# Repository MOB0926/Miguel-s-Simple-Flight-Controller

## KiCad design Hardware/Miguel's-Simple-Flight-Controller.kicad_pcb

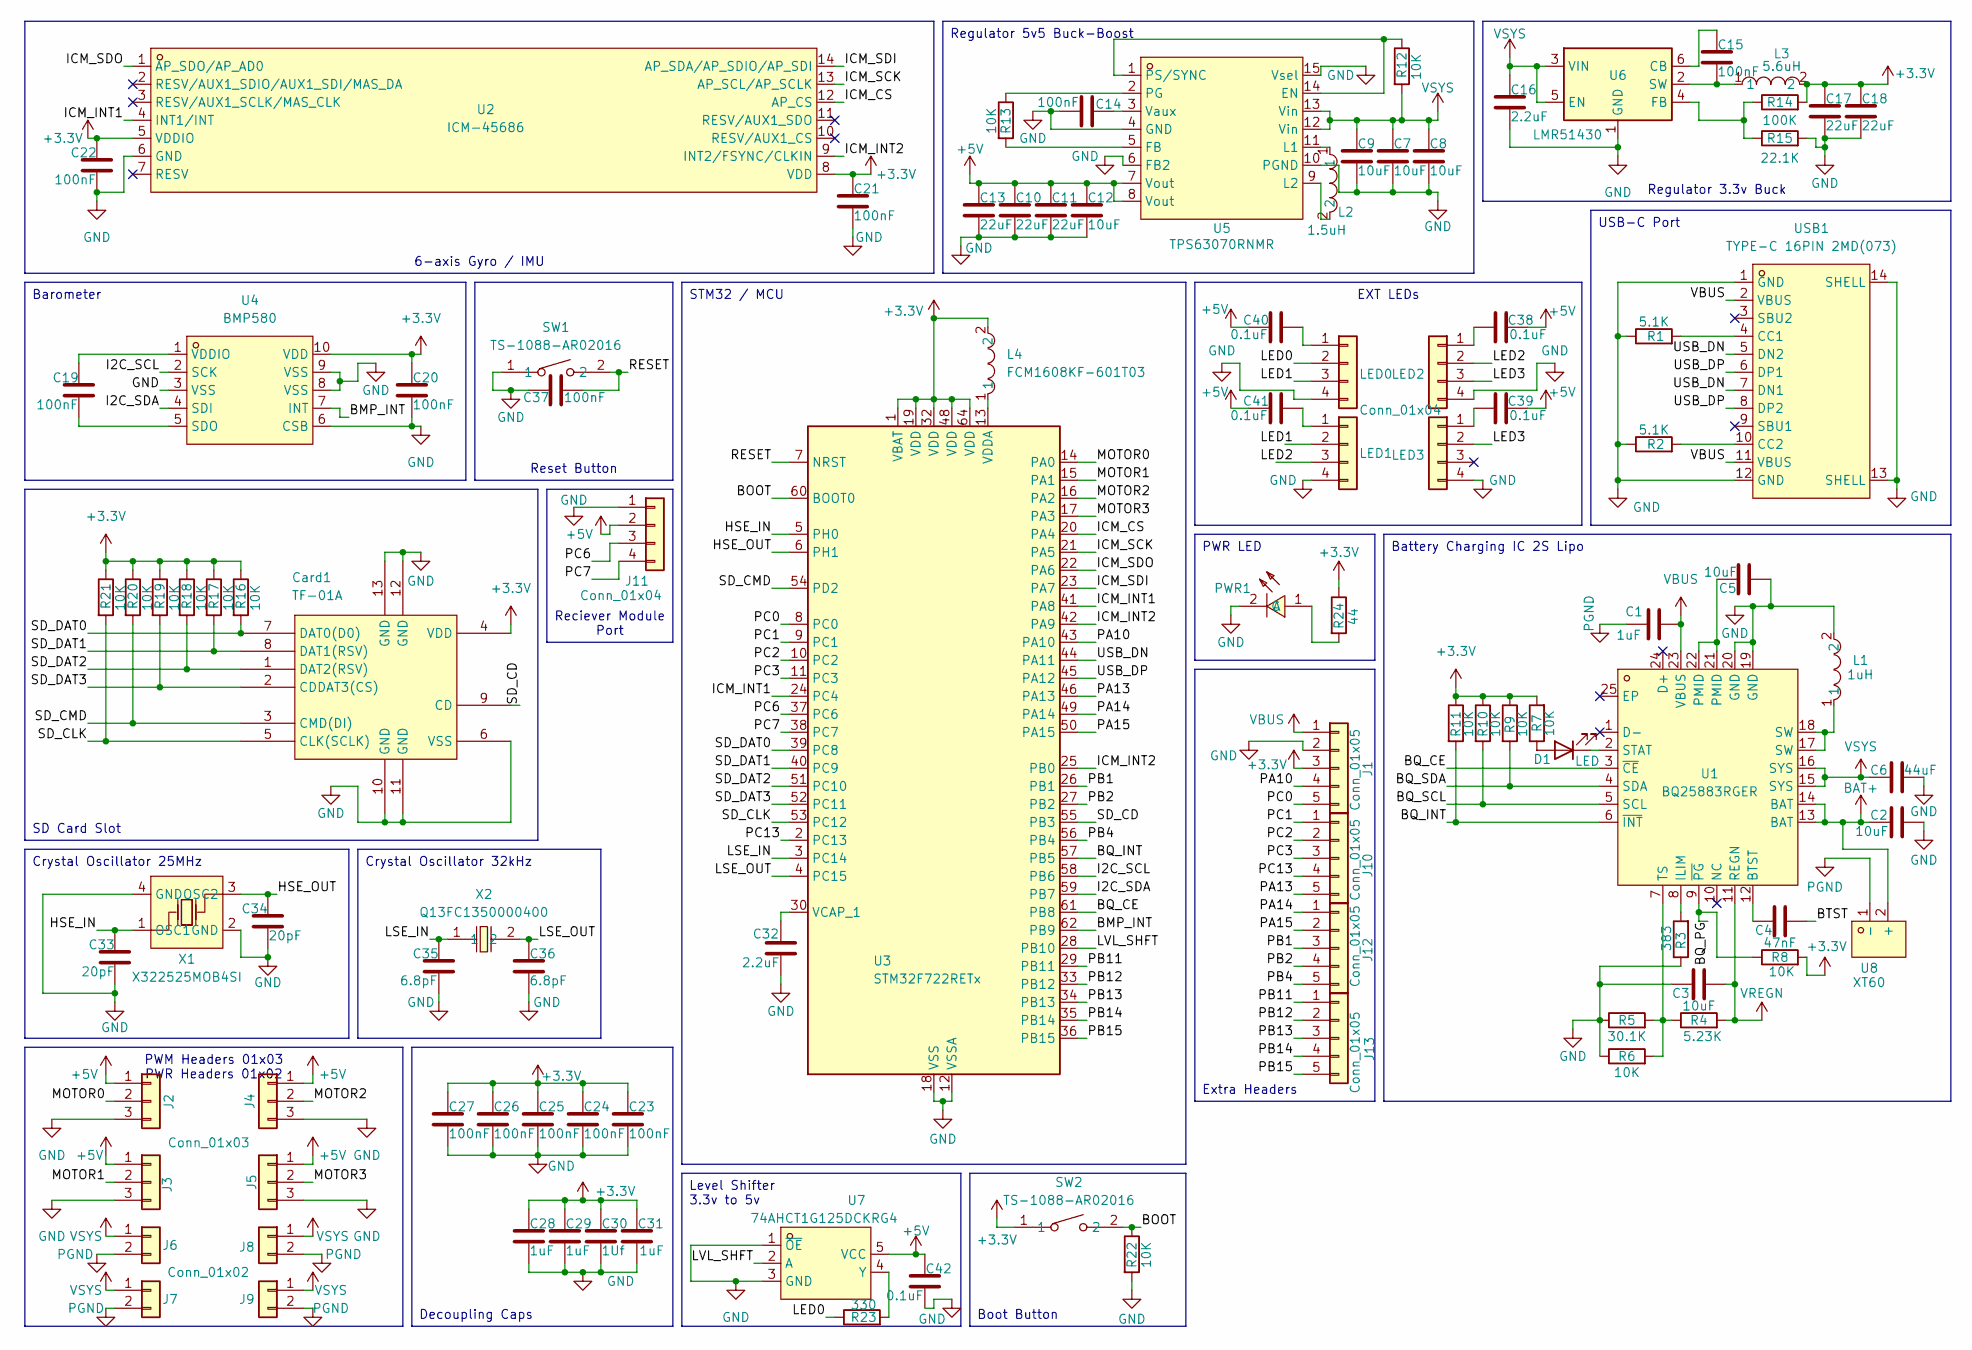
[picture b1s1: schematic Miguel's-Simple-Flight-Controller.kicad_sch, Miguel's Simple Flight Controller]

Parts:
C1, C28, C29, C31: 1uF; C_0402_1005Metric
C2, C3, C5, C7, C8, C9, C12: 10uF; C_0402_1005Metric
C4: 47nF; C_0402_1005Metric
C6: 44uF; C_0805_2012Metric
C10, C11, C13, C17, C18: 22uF; C_0805_2012Metric
C14, C15, C19, C20, C21, C22, C23, C24, C25, C26, C27, C37: 100nF; C_0402_1005Metric
C16, C32: 2.2uF; C_0402_1005Metric
C30: 1Uf; C_0402_1005Metric
C33, C34: 20pF; C_0402_1005Metric
C35, C36: 6.8pF; C_0402_1005Metric
C38, C39, C40, C41, C42: 0.1uF; C_0402_1005Metric
Card1: TF-01A; TF-SMD_TF-01A; LCSC Part C91145
D1: LED; LED0402-R-RD
J1, J10, J12, J13: Conn_01x05; PinHeader_1x05_P2.54mm_Vertical
J2, J3, J4, J5: Conn_01x03; PinHeader_1x03_P2.54mm_Vertical
J6, J7, J8, J9: Conn_01x02; PinHeader_1x02_P2.54mm_Vertical
J11: Conn_01x04; PinHeader_1x04_P2.54mm_Vertical
L1: 1uH; L2520; LCSC Part C435392
L2: 1.5uH; IND-SMD_L4.0-W4.0-A; LCSC Part C3033018
L3: 5.6uH; IND-SMD_L3.0-W3.0; LCSC Part C18236327
L4: FCM1608KF-601T03; L0603; LCSC Part C141723
LED0, LED1, LED2, LED3: Conn_01x04; PinHeader_1x04_P2.54mm_Vertical
PWR1: 16-213/GHC-YR1S1/3T; LED0402-R-RD; LCSC Part C74338
R1, R2: 5.1K; R_0201_0603Metric
R3: 383; R_0201_0603Metric
R4: 5.23K; R_0201_0603Metric
R5: 30.1K; R_0201_0603Metric
R6, R7, R8, R9, R10, R11, R12, R13, R16, R17, R18, R19, R20, R21, R22: 10K; R_0201_0603Metric
R14: 100K; R_0402_1005Metric
R15: 22.1K; R_0201_0603Metric
R23: 330; R_0201_0603Metric
R24: 44; R_0201_0603Metric
SW1, SW2: TS-1088-AR02016; SW-SMD_L3.9-W3.0-P4.45; LCSC Part C720477
U1: BQ25883RGER; VFQFPN-24_L4.0-W4.0-P0.50-BL-EP2.8; LCSC Part C544362
U2: ICM-45686; LGA-14_L3.0-W2.5-P0.50-TL; LCSC Part C22459454
U3: STM32F722RETx; LQFP-64_10x10mm_P0.5mm
U4: BMP580; LGA-10_L2.0-W2.0-P0.50-TL_BMP580; LCSC Part C22391138
U5: TPS63070RNMR; VQFN-HR-15_L3.0-W2.5-P0.50-BL_TPS63070RNMR; LCSC Part C109322
U6: LMR51430; SOT-23-6
U7: 74AHCT1G125DCKRG4; SC-70-5_L2.1-W1.3-P0.65-LS2.1-BR; LCSC Part C2675692
U8: XT60; CONN-TH_XT60; LCSC Part C98733
USB1: TYPE-C 16PIN 2MD(073); USB-C-SMD_TYPE-C-6PIN-2MD-073; LCSC Part C2765186
X1: X322525MOB4SI; CRYSTAL-SMD_4P-L3.2-W2.5-BL; LCSC Part C9006
X2: Q13FC1350000400; FC-135R_L3.2-W1.5; LCSC Part C32346

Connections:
+3.3V: C17.1, C18.1, C20.1, C21.1, C22.1, C23.1, C24.1, C25.1, C26.1, C27.1, C28.1, C29.1, C30.1, C31.1, Card1.4 (VDD), J1.3, L3.2, L4.2, R7.2, R8.2, R9.1, R10.1, R11.1, R14.2, R16.1, R17.1, R18.1, R19.1, R20.1, R21.1, R24.1, SW2.1, U2.5 (VDDIO), U2.8 (VDD), U3.1 (VBAT), U3.19 (VDD), U3.32 (VDD), U3.48 (VDD), U3.64 (VDD), U4.10 (VDD)
+5V: C10.1, C11.1, C12.1, C13.1, C38.2, C39.2, C40.2, C41.2, C42.1, J2.1, J3.1, J4.1, J5.1, J11.2, U5.7 (Vout), U5.8 (Vout), U7.5 (VCC)
/BMP_INT: U3.62 (PB9), U4.7 (INT)
/BOOT: R22.1, SW2.2, U3.60 (BOOT0)
/BQ_CE: U1.3 (~CE), U3.61 (PB8)
/BQ_INT: R11.2, U1.6 (~INT), U3.57 (PB5)
/BQ_PG: R8.1, U1.9 (~PG)
/BQ_SCL: R10.2, U1.5 (SCL)
/BQ_SDA: R9.2, U1.4 (SDA)
/BTST: C4.2
/HSE_IN: C33.1, U3.5 (PH0), X1.1 (OSC1)
/HSE_OUT: C34.1, U3.6 (PH1), X1.3 (OSC2)
/I2C_SCL: U3.58 (PB6), U4.2 (SCK)
/I2C_SDA: U3.59 (PB7), U4.4 (SDI)
/ICM_CS: U2.12 (AP_CS), U3.20 (PA4)
/ICM_INT1: U2.4 (INT1/INT), U3.24 (PC4), U3.41 (PA8)
/ICM_INT2: U2.9 (INT2/FSYNC/CLKIN), U3.25 (PB0), U3.42 (PA9)
/ICM_SCK: U2.13 (AP_SCL/AP_SCLK), U3.21 (PA5)
/ICM_SDI: U2.14 (AP_SDA/AP_SDIO/AP_SDI), U3.23 (PA7)
/ICM_SDO: U2.1 (AP_SDO/AP_AD0), U3.22 (PA6)
/LED0: LED0.2, R23.1
/LED1: LED0.3, LED1.2
/LED2: LED1.3, LED2.2
/LED3: LED2.3, LED3.2
/LSE_IN: C35.1, U3.3 (PC14), X2.1
/LSE_OUT: C36.1, U3.4 (PC15), X2.2
/LVL_SHFT: U3.28 (PB10), U7.2 (A)
/MOTOR0: J2.2, U3.14 (PA0)
/MOTOR1: J3.2, U3.15 (PA1)
/MOTOR2: J4.2, U3.16 (PA2)
/MOTOR3: J5.2, U3.17 (PA3)
/PA10: J1.4, U3.43 (PA10)
/PA13: J10.5, U3.46 (PA13)
/PA14: J12.1, U3.49 (PA14)
/PA15: J12.2, U3.50 (PA15)
/PB1: J12.3, U3.26 (PB1)
/PB2: J12.4, U3.27 (PB2)
/PB4: J12.5, U3.56 (PB4)
/PB11: J13.1, U3.29 (PB11)
/PB12: J13.2, U3.33 (PB12)
/PB13: J13.3, U3.34 (PB13)
/PB14: J13.4, U3.35 (PB14)
/PB15: J13.5, U3.36 (PB15)
/PC0: J1.5, U3.8 (PC0)
/PC1: J10.1, U3.9 (PC1)
/PC2: J10.2, U3.10 (PC2)
/PC3: J10.3, U3.11 (PC3)
/PC6: J11.3, U3.37 (PC6)
/PC7: J11.4, U3.38 (PC7)
/PC13: J10.4, U3.2 (PC13)
/RESET: C37.2, SW1.2, U3.7 (NRST)
/SD_CD: Card1.9 (CD), U3.55 (PB3)
/SD_CLK: Card1.5 (CLK(SCLK)), R21.2, U3.53 (PC12)
/SD_CMD: Card1.3 (CMD(DI)), R20.2, U3.54 (PD2)
/SD_DAT0: Card1.7 (DAT0(D0)), R16.2, U3.39 (PC8)
/SD_DAT1: Card1.8 (DAT1(RSV)), R17.2, U3.40 (PC9)
/SD_DAT2: Card1.1 (DAT2(RSV)), R18.2, U3.51 (PC10)
/SD_DAT3: Card1.2 (CDDAT3(CS)), R19.2, U3.52 (PC11)
/USB_DN: U3.44 (PA11), USB1.5 (DN2), USB1.7 (DN1)
/USB_DP: U3.45 (PA12), USB1.6 (DP1), USB1.8 (DP2)
BAT+: C2.1, U1.13 (BAT), U1.14 (BAT), U8.2 (+)
GND: C2.2, C3.1, C5.2, C6.2, C7.2, C8.2, C9.2, C10.2, C11.2, C12.2, C13.2, C14.1, C16.2, C17.2, C18.2, C20.2, C21.2, C22.2, C23.2, C24.2, C25.2, C26.2, C27.2, C28.2, C29.2, C30.2, C31.2, C32.2, C33.2, C34.2, C35.2, C36.2, C37.1, C42.2, Card1.6 (VSS), Card1.10 (GND), Card1.11 (GND), Card1.12 (GND), Card1.13 (GND), J1.2, J2.3, J3.3, J4.3, J5.3, J11.1, L1.2, LED0.4, LED1.4, LED2.4, LED3.4, PWR1.2 (C), R1.1, R2.1, R3.1, R5.1, R6.1, R15.2, R22.2, SW1.1, U1.19 (GND), U1.20 (GND), U2.6 (GND), U3.12 (VSSA), U3.18 (VSS), U3.31 (VSS), U3.47 (VSS), U3.63 (VSS), U4.3 (VSS), U4.6 (CSB), U4.8 (VSS), U4.9 (VSS), U5.4 (GND), U5.6 (FB2), U5.10 (PGND), U5.15 (Vsel), U6.1 (GND), U7.1 (~OE), U7.3 (GND), USB1.1 (GND), USB1.12 (GND), USB1.13 (SHELL), USB1.14 (SHELL), X1.2 (GND), X1.4 (GND)
unnamed: C5.1, U1.21 (PMID), U1.22 (PMID)
unnamed: D1.2 (A), R7.1
unnamed: D1.1 (K), U1.2 (STAT)
unnamed: L1.1, U1.17 (SW), U1.18 (SW)
unnamed: C40.1, LED0.1
unnamed: C41.1, LED1.1
unnamed: C38.1, LED2.1
unnamed: C39.1, LED3.1
unnamed: PWR1.1 (A), R24.2
unnamed: C4.1, U1.12 (BTST)
unnamed: R3.2, U1.8 (ILIM)
unnamed: R4.1, R5.2, R6.2, U1.7 (TS)
unnamed: C32.1, U3.30 (VCAP_1)
unnamed: L4.1, U3.13 (VDDA)
unnamed: C19.2, U4.5 (SDO)
unnamed: C19.1, U4.1 (VDDIO)
unnamed: R12.1, U5.1 (PS/SYNC), U5.14 (EN)
unnamed: R13.2, U5.5 (FB)
unnamed: L2.1, U5.11 (L1)
unnamed: L2.2, U5.9 (L2)
unnamed: R13.1, U5.2 (PG)
unnamed: C14.2, U5.3 (Vaux)
unnamed: C15.1, U6.6 (CB)
unnamed: R14.1, R15.1, U6.4 (FB)
unnamed: C15.2, L3.1, U6.2 (SW)
unnamed: R23.2, U7.4 (Y)
unnamed: R1.2, USB1.4 (CC1)
unnamed: R2.2, USB1.10 (CC2)
PGND: C1.1, J6.2, J7.2, J8.2, J9.2, U8.1 (-)
VBUS: C1.2, J1.1, U1.23 (VBUS), USB1.2 (VBUS), USB1.11 (VBUS)
VREGN: C3.2, R4.2, U1.11 (REGN)
VSYS: C6.1, C7.1, C8.1, C9.1, C16.1, J6.1, J7.1, J8.1, J9.1, R12.2, U1.15 (SYS), U1.16 (SYS), U5.12 (Vin), U5.13 (Vin), U6.3 (VIN), U6.5 (EN)

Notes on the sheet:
Reset Button
EXT LEDs
USB-C Port
Level Shifter 3.3v to 5v
Regulator 3.3v Buck
Crystal Oscillator 25MHz
Extra Headers
PWR LED
Decoupling Caps
6-axis Gyro / IMU
Crystal Oscillator 32kHz
Boot Button
Regulator 5v5 Buck-Boost
PWM Headers 01x03 PWR Headers 01x02
Barometer
SD Card Slot
STM32 / MCU
Battery Charging IC 2S Lipo
Reciever Module Port

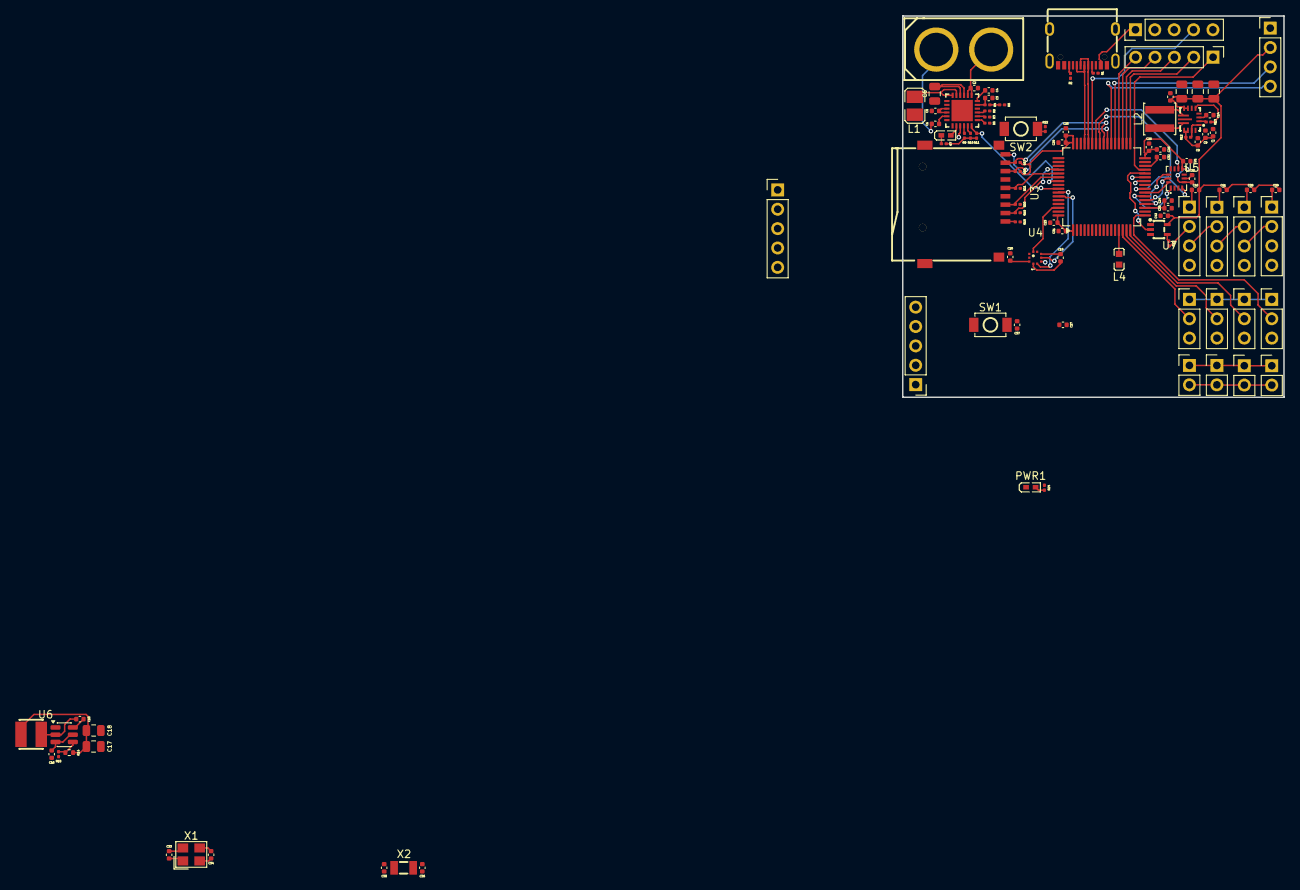
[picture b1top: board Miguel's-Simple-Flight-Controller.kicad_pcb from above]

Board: 2 copper layers, 50.0 x 50.0 mm, 103 parts (0 on the bottom side), 93 nets.

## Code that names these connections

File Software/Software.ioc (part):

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Mcu.Name=STM32F722R(C-E)Tx
Mcu.Package=LQFP64
Mcu.UserName=STM32F722RETx
PA0-WKUP.Signal=S_TIM5_CH1
PA1.Signal=S_TIM5_CH2
PA11.Mode=Host_Only
PA11.Signal=USB_OTG_FS_DM
PA12.Mode=Host_Only
PA12.Signal=USB_OTG_FS_DP
PA2.Signal=S_TIM5_CH3
PA3.Signal=S_TIM5_CH4
PA4.Mode=NSS_Signal_Hard_Output
PA4.Signal=SPI1_NSS
PA5.Mode=Full_Duplex_Master
PA5.Signal=SPI1_SCK
PA6.Mode=Full_Duplex_Master
PA6.Signal=SPI1_MISO
PA7.Mode=Full_Duplex_Master
PA7.Signal=SPI1_MOSI
PB0.Signal=GPXTI0
PB10.Signal=S_TIM2_CH3
PB3.Signal=GPIO_Input
PB5.Signal=GPXTI5
PB6.Mode=I2C
PB6.Signal=I2C1_SCL
PB7.Mode=I2C
PB7.Signal=I2C1_SDA
PB8.Signal=GPIO_Output
PC10.Mode=SD_4_bits_Wide_bus
PC10.Signal=SDMMC1_D2
PC11.Mode=SD_4_bits_Wide_bus
PC11.Signal=SDMMC1_D3
PC12.Mode=SD_4_bits_Wide_bus
PC12.Signal=SDMMC1_CK
PC14-OSC32_IN.Mode=LSE-External-Oscillator
PC14-OSC32_IN.Signal=RCC_OSC32_IN
PC15-OSC32_OUT.Mode=LSE-External-Oscillator
PC15-OSC32_OUT.Signal=RCC_OSC32_OUT
PC4.Signal=GPXTI4
PC6.Mode=Asynchronous
PC6.Signal=USART6_TX
PC7.Mode=Asynchronous
PC7.Signal=USART6_RX
PC8.Mode=SD_4_bits_Wide_bus
PC8.Signal=SDMMC1_D0
PC9.Mode=SD_4_bits_Wide_bus
PC9.Signal=SDMMC1_D1
PD2.Mode=SD_4_bits_Wide_bus
PD2.Signal=SDMMC1_CMD
PH0-OSC_IN.Mode=HSE-External-Oscillator
PH0-OSC_IN.Signal=RCC_OSC_IN
PH1-OSC_OUT.Mode=HSE-External-Oscillator
PH1-OSC_OUT.Signal=RCC_OSC_OUT
RCC.HSE_VALUE=25000000
board=custom

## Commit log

2026-01-15 setup
2026-01-15 Fixing EasyEDA2Kicad issues
2026-01-18 Schematic Done
2026-01-18 Schematic Pretty-Much Done
    Just missing Footprint assignation
2026-01-20 Started on PCB
2026-04-01 Rename project to 'Miguel's Flight Controller'
